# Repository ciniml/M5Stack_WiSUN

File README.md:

# M5Stack用 Wi-SUN拡張モジュール

## 概要

M5StackにロームのWi-SUNモジュール BP35A1 をつなぐための拡張モジュールの設計データ

* [動画](https://youtu.be/MU2Bb5bknPw)

## ファームウェア

* ビルド済みのカスタムMicroPythonバイナリと、pythonディレクトリに入っているスクリプトを含むSPIFFSイメージを書き込むように設定したM5BurnerをOneDriveに置いてあるので適当に使ってください。

https://1drv.ms/f/s!AvgeuJrD0ORom7oEdzDq509qd-Dngg

* M5Stackの公式にM5Burnerの再配布の許可をもらおうとTwitterでmentionを送ったら、公式の方に含めていただけることになりましたので、公式M5BurnerにあるWiSUNというファームを書き込むのでも良いです。

### 機能

* スマートメーターから瞬時電力、瞬時電流、積算電力量を取得してM5Stackの画面に簡易表示
* SORACOM Inventory + SORACOM Harvestを使って上記データを収集・可視化

### 使い方

1. ファームウェアを書き込んだあと、USBケーブルをPCにつないだままでTeraTermなどのターミナルでM5Stackのシリアルポートを開きます。
2. リセットがかかって、そのうち `Input SSID:` とプロンプトが表示されますので、接続先Wi-FiアクセスポイントのSSIDを入力してEnterを押します。
3. 次に `Input Password:` と表示されますのでWi-Fi接続のパスワードを入力します。 (*で隠されたりしないので、覗き見られないように注意してください。)
4. そのまましばらくすると M5StackのIPアドレスを表示したのち、`appconfig` が無いというエラーで停止し、 REPLの状態になります。
5. M5Stackの同一ネットワークにいるPCからWinSCPなどの`FTP`クライアント機能で (4)に表示されたアドレスに接続します。ユーザー名とパスワードは両方とも `esp32` です。
6. FTP経由でのファイル転送が可能になりますので、appconfig.pyという名前で以下の内容のファイルを作って M5Stackの `/flash` 以下にアップロードします。

```python
wifi_ssid = 'Wi-FiのSSID'
wifi_password = 'Wi-Fiのパスワード'
route_b_id = 'Route BのID (電力会社から教えてもらうやつ)'
route_b_password = 'Route Bのパスワード (電力会社から教えてもらうやつ)'
inventory_id = 'SORACOM InventoryのデバイスID'
inventory_password = 'SORACOM Inventoryのデバイス用パスワード'
```

7. M5Stackのリセットボタンを押してリセットします。

## (書きかけ)

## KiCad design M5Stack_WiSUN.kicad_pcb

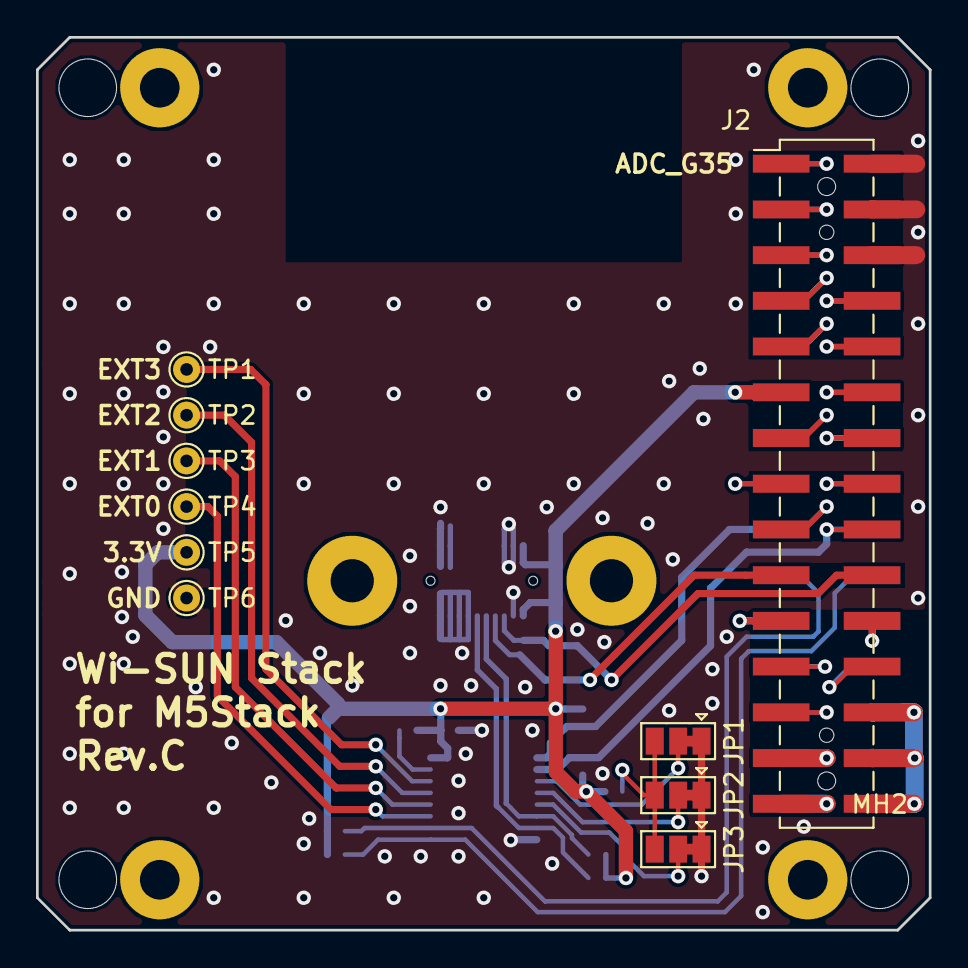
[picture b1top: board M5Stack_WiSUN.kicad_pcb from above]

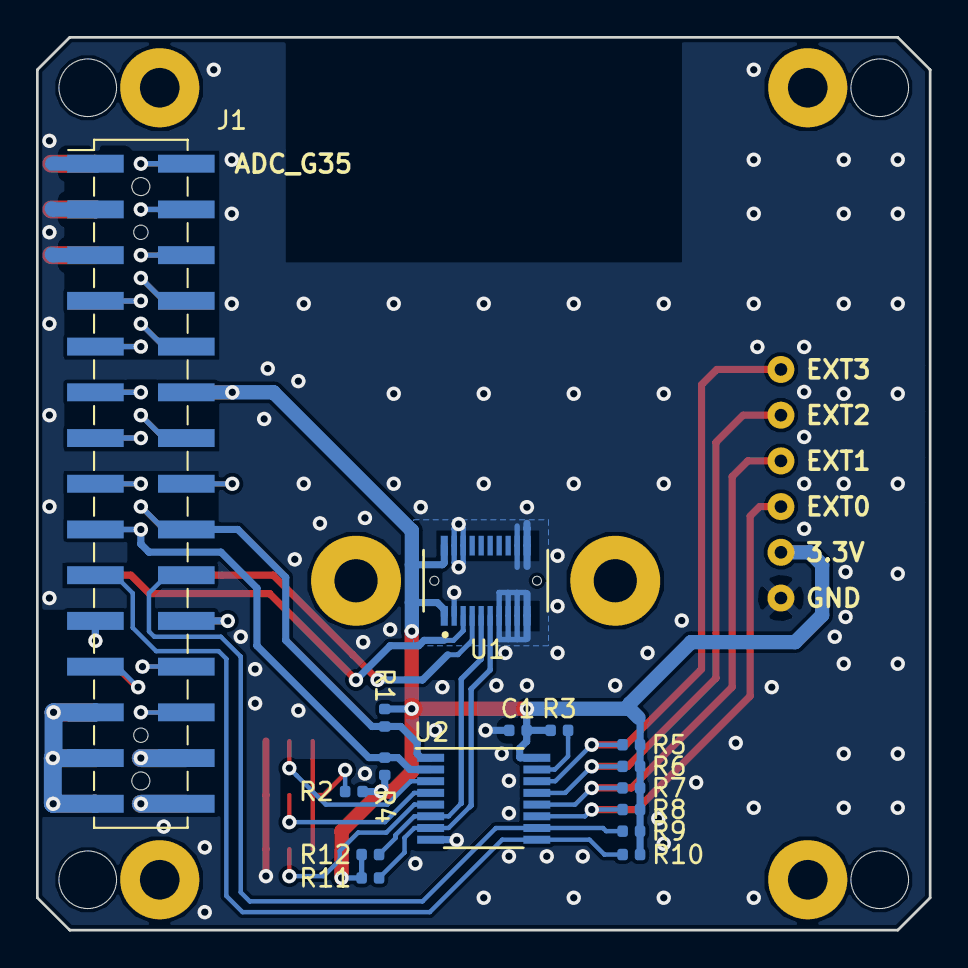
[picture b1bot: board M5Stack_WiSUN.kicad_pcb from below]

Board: 2 copper layers, 49.6 x 49.6 mm, 34 parts (16 on the bottom side), 39 nets.

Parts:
C1: 100n; C_0402_1005Metric
J1: MBUS_BOTTOM; MBUS_Socket
J2: MBUS_TOP; MBUS_Header
JP1, JP2, JP3: Jumper_3_Bridged12; SolderJumper-3_P1.3mm_Bridged12_Pad1.0x1.5mm
MH1, MH2, MH3, MH4: Corner; MountingHole_3.2mm_M3
MH5, MH6, MH7, MH8: Fix; MountingHole_2.2mm_M2_Pad
R1, R2, R3, R4: 2k; R_0402_1005Metric
R5, R6, R7, R8, R9, R10, R11, R12: 100k; R_0402_1005Metric
TP1, TP2, TP3, TP4, TP5, TP6: TestPoint; TestPoint_THTPad_D1.5mm_Drill0.7mm
U1: BP35A1
U2: PCA9557; TSSOP-16_4.4x5mm_P0.65mm

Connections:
+3V3: C1.1, J1.12, J2.11, R1.1, R2.1, R3.2, R4.1, R5.1, R6.1, R7.1, R8.1, R9.1, R10.1, R11.1, R12.1, TP5.1, U1.1, U1.11, U2.16
+5V: J1.28, J2.27
/A0: JP1.2, U2.3
/A1: JP2.2, U2.4
/A2: JP3.2, U2.5
/ADC_G35: J1.2, J2.1
/ADC_G36: J1.4, J2.3
/BATTERY: J1.30, J2.29
/BP35_RESET: R11.2, U1.6, U2.7
/BP35_WKUP: R12.2, U1.5, U2.6
/DAC: J1.10, J2.9
/DAC_SPK: J1.8, J2.7
/EXT0: R8.2, TP4.1, U2.11
/EXT1: R7.2, TP3.1, U2.12
/EXT2: R6.2, TP2.1, U2.13
/EXT3: R5.2, TP1.1, U2.14
/GPIO_G2: J2.20, U1.3
/GPIO_G2_R: J1.19, R10.2, U2.9
/GPIO_G5: J2.19, U1.4
/GPIO_G5_R: J1.20, R9.2, U2.10
/HPWR: J1.25, J1.27, J1.29, J2.26, J2.28, J2.30
/IIS_IN: J1.26, J2.25
/IIS_MK: J1.24, J2.23
/IIS_OUT: J1.23, J2.24
/IIS_SK: J1.21, J2.22
/IIS_WS: J1.22, J2.21
/MISO: J1.9, J2.10
/MOSI: J1.7, J2.8
/RST: J1.6, J2.5
/RXD0: J1.13, J2.14
/RXD2: J1.15, J2.16
/SCK: J1.11, J2.12
/SCL: J1.18, J2.17, R1.2, U2.1
/SDA: J1.17, J2.18, R4.2, U2.2
/TXD0: J1.14, J2.13
/TXD2: J1.16, J2.15
GND: C1.2, J1.1, J1.3, J1.5, J2.2, J2.4, J2.6, JP1.1, JP2.1, JP3.1, TP6.1, U1.2, U1.7, U1.8, U1.9, U1.10, U1.12, U1.13, U1.19, U1.20, U2.8
unnamed: JP1.3, JP2.3, JP3.3, R2.2
unnamed: R3.1, U2.15

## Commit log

2018-10-09 Implement BP35 driver and EchonetLiteFrame
2018-10-09 Add LICENSE
2018-10-27 PCB revision B
2018-10-27 Change BP35A1 module to support Rev.B PCB (no longer supports Rev.A PCB)
2019-01-05 Add bootstrap to support the latest M5Stack_MicroPython
2019-01-05 Move BP35A1 to bottom side. Use I2C IO expander to control BP35A1 reset and wake pins.
2019-01-20 Revision C
2019-01-20 Add encrosure source
2019-02-14 Update to support rev.C board
2019-02-14 Update enclosure
2019-02-14 Add README
2019-03-14 fix that FTP username/password is not described.
2019-03-14 Improve screen design
2019-03-14 Add screenshot
2019-03-15 Add movie
2019-03-15 Fix that embedded movie is not working
2019-04-09 Update firmware startup code
2019-10-29 Add UI Flow modulesX
